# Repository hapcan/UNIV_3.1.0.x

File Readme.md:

UNIV 3.1.0.x
============

BUTTON MODULE - 8 close/open inputs

Device webpage: http://hapcan.com/devices/universal/univ_3/univ_3-1-0-x/

Hardware created in Eagle PCB Software http://www.cadsoftusa.com/

Firmware created in Microchip MPLAB http://www.microchip.com/mplabide/ in assembly language

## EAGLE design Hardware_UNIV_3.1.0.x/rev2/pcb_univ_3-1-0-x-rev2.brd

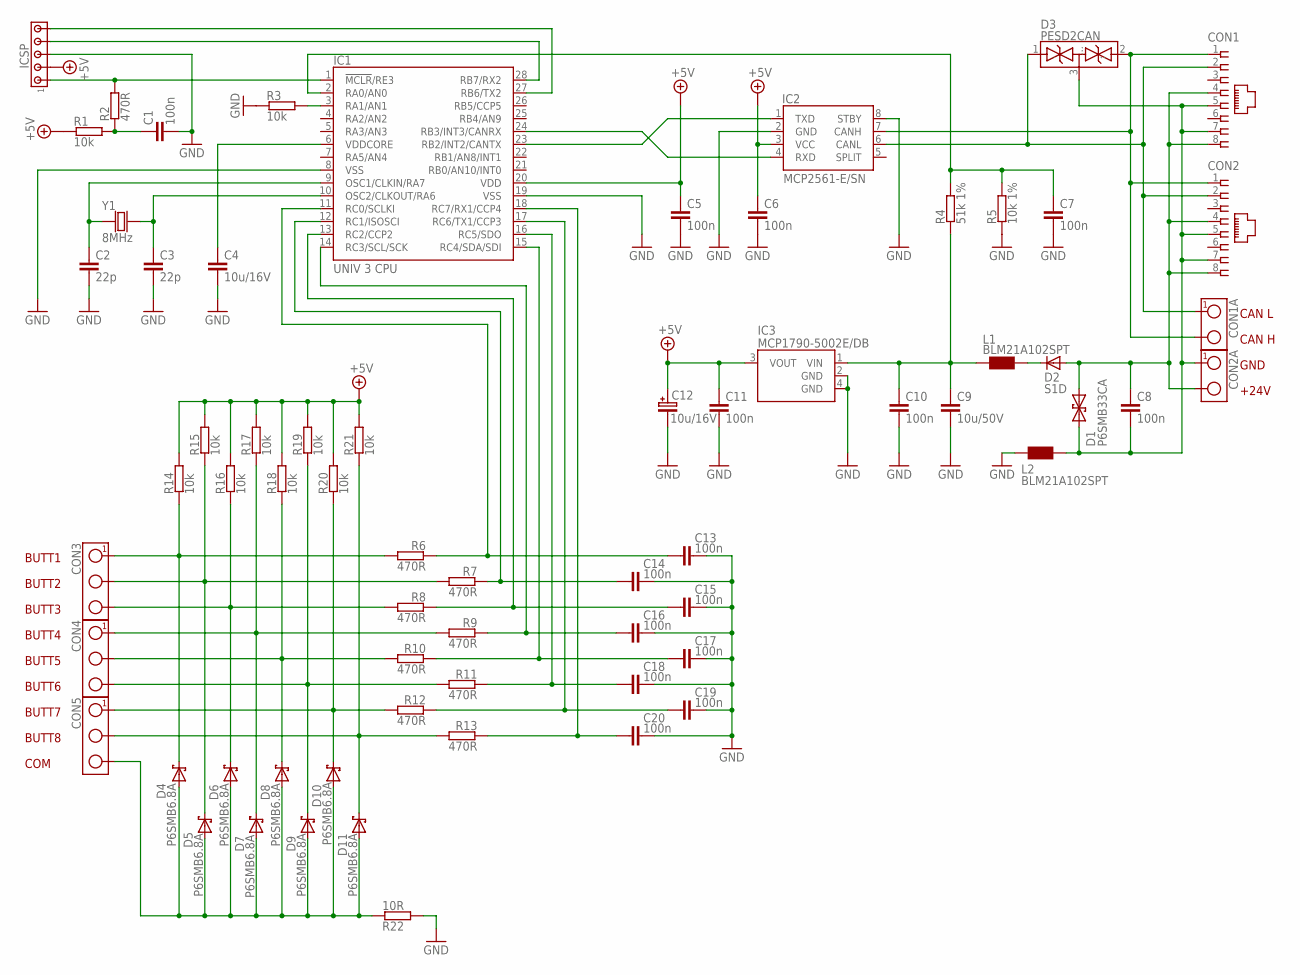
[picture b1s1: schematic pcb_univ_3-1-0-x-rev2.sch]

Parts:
C1, C5, C6, C7, C8, C10, C11, C13, C14, C15, C16, C17, C18, C19, C20: 100n; 0805
C2, C3: 22p; 0805
C4: 10u/16V; 0805
C9: 10u/50V; 1210
C12: 10u/16V; SMC_B
CON1, CON2: RJ45-SOCKET; RJ45-PCB-SOCKET
CON1A, CON2A: TERMINAL-2; ARK2-5X10,5MM
CON3, CON4, CON5: TERMINAL-3; ARK3-5X10.5MM
D1: P6SMB33CA; DO-214_TRANSIL2
D2: S1D; DO-214
D3: PESD2CAN; SOT-23
D4, D5, D6, D7, D8, D9, D10, D11: P6SMB6.8A; DO-214
IC1: UNIV 3 CPU; UNIV3CPU
IC2: MCP2561-E/SN; SO-08
IC3: MCP1790-5002E/DB; SOT-223
ICSP: HEADER5; SIP-5
L1, L2: BLM21A102SPT; 0805
R1, R3, R14, R15, R16, R17, R18, R19, R20, R21: 10k; 0805
R2, R6, R7, R8, R9, R10, R11, R12, R13: 470R; 0805
R4: 51k 1%; 0805
R5: 10k 1%; 0805
R22: 10R; 0805
Y1: 8MHz; CRYSTAL-HC49V

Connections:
+5V: C5.1, C6.1, C11.1, C12.+ (1), IC1.20 (VDD), IC2.3 (VCC), IC3.3 (VOUT), ICSP.2, R1.1, R14.2, R15.2, R16.2, R17.2, R18.2, R19.2, R20.2, R21.2
GND: C1.2, C2.2, C3.2, C4.2, C5.2, C6.2, C7.2, C9.2, C10.2, C11.2, C12.- (2), C13.2, C14.2, C15.2, C16.2, C17.2, C18.2, C19.2, C20.2, IC1.8 (VSS), IC1.19 (VSS), IC2.2 (GND), IC2.8 (STBY), IC3.2 (GND), IC3.4 (GND), ICSP.3, L2.1, R3.1, R5.1, R22.2
unnamed: CON5.3, D4.A, D5.A, D6.A, D7.A, D8.A, D9.A, D10.A, D11.A, R22.1
unnamed: IC1.24 (RB3/INT3/CANRX), IC2.4 (RXD)
unnamed: IC1.23 (RB2/INT2/CANTX), IC2.1 (TXD)
unnamed: CON1.1, CON1A.2, CON2.1, D3.2 (..), IC2.7 (CANH)
unnamed: CON3.1, D4.C, R6.2, R14.1
unnamed: CON3.3, D6.C, R8.2, R16.1
unnamed: C1.1, R1.2, R2.1
unnamed: IC1.1 (!MCLR!/RE3), ICSP.1, R2.2
unnamed: C8.1, CON1.4, CON1.8, CON2.4, CON2.8, CON2A.2, D1.A (1), D2.A
unnamed: IC1.28 (RB7/RX2), ICSP.4
unnamed: C14.1, IC1.12 (RC1/ISOSCI), R7.1
unnamed: IC1.3 (RA1/AN1), R3.2
unnamed: CON3.2, D5.C, R7.2, R15.1
unnamed: IC1.27 (RB6/TX2), ICSP.5
unnamed: C3.1, IC1.10 (OSC2/CLKOUT/RA6), Y1.2
unnamed: C7.1, IC1.2 (RA0/AN0), R4.2, R5.2
unnamed: C9.1, C10.1, IC3.1 (VIN), L1.1, R4.1
unnamed: C8.2, CON1.5, CON1.7, CON2.5, CON2.7, CON2A.1, D1.C (2), D3.3 (...), L2.2
unnamed: C15.1, IC1.13 (RC2/CCP2), R8.1
unnamed: CON4.1, D7.C, R9.2, R17.1
unnamed: C16.1, IC1.14 (RC3/SCL/SCK), R9.1
unnamed: CON4.3, D9.C, R11.2, R19.1
unnamed: CON5.1, D10.C, R12.2, R20.1
unnamed: C13.1, IC1.11 (RC0/SCLKI), R6.1
unnamed: CON1.2, CON1A.1, CON2.2, D3.1 (.), IC2.6 (CANL)
unnamed: C17.1, IC1.15 (RC4/SDA/SDI), R10.1
unnamed: CON4.2, D8.C, R10.2, R18.1
unnamed: CON5.2, D11.C, R13.2, R21.1
unnamed: C2.1, IC1.9 (OSC1/CLKIN/RA7), Y1.1
unnamed: C18.1, IC1.16 (RC5/SDO), R11.1
unnamed: C19.1, IC1.17 (RC6/TX1/CCP3), R12.1
unnamed: C20.1, IC1.18 (RC7/RX1/CCP4), R13.1
unnamed: C4.1, IC1.6 (VDDCORE)
unnamed: D2.C, L1.2

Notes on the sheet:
BUTT2
BUTT3
BUTT4
BUTT5
BUTT6
COM
BUTT1
BUTT7
BUTT8
CAN L
CAN H
GND
+24V

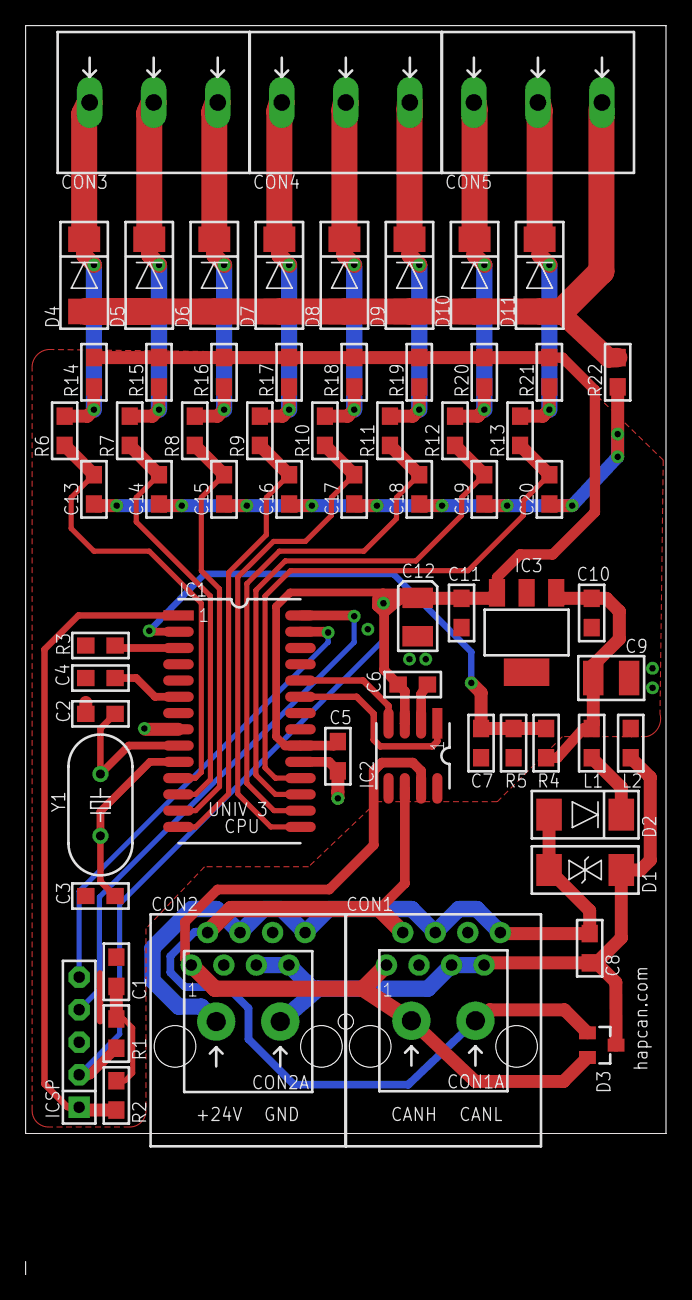
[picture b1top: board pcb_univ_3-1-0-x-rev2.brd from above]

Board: 2 copper layers, 50.0 x 86.5 mm, 67 parts (0 on the bottom side), 36 nets.

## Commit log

2013-09-25 hardware revision 1
2013-09-25 firmware revision 0
2015-10-12 hardware UNIV 3.1.0.x revision 1
2015-10-12 hardware UNIV 3.1.0.x revision 2
2016-05-04 firmware UNIV 3.1.0.0 revision 1
2016-12-27 firmware UNIV 3.1.0.0 revision 2
2022-10-31 firmware UNIV 3.1.0.0 revision 3
2022-10-31 MIT license
